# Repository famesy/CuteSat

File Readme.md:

# CubeSat PCB Design for Reliable Space Missions

CubeSat is an affordable and popular educational platform for deploying payloads into orbit. However, many university-level missions fail at a rate of around 50%. The primary reason for this is the difficulty of adapting an existing design, which results in poorly designed hardware for the harsh environment of space and a lack of failure handling software.

To address this problem, we have developed an expandable, low-cost printed circuit board (PCB) that can be stacked and includes the following components:

- Power supply unit
- Microcontroller
- Several sensors
- Watchdog
- Communication bus isolation
- External memory

We have used a component selection methodology that is based on existing research and adapted it to our design. We have also implemented a software Hamming error-correction code to protect the data.

Since our PCBs are modular, readers can design their own system using our design as a starting point. We offer failure handler software and hardware that can be easily integrated into their design. Our ultimate goal is to make space studies more accessible to everyone, increase the success rate, and allow people to focus on their missions rather than the hectic development.

Lastly, we intend to make our project open source so that it can continue to grow and improve over time. We hope that this project will develop into a community where people can discuss their designs and share their changes and knowledge for various missions.

Thank you for considering our CubeSat PCB design for your space mission needs.

## Project Components
This project includes two distinct folders: hardware and software.

### Hardware
The hardware folder contains four PCB designs that were used in our mission:

#### MCU (base PCB)

#### Motor driver (payload PCB)

#### Encoder (payload PCB)

#### ST-Link adapter

### Software
The software folder contains STM32 projects that include libraries for interfacing with the sensors and implementing error detection and correction algorithms.

### How its look when assemble

####Thank you for your interest in our project!

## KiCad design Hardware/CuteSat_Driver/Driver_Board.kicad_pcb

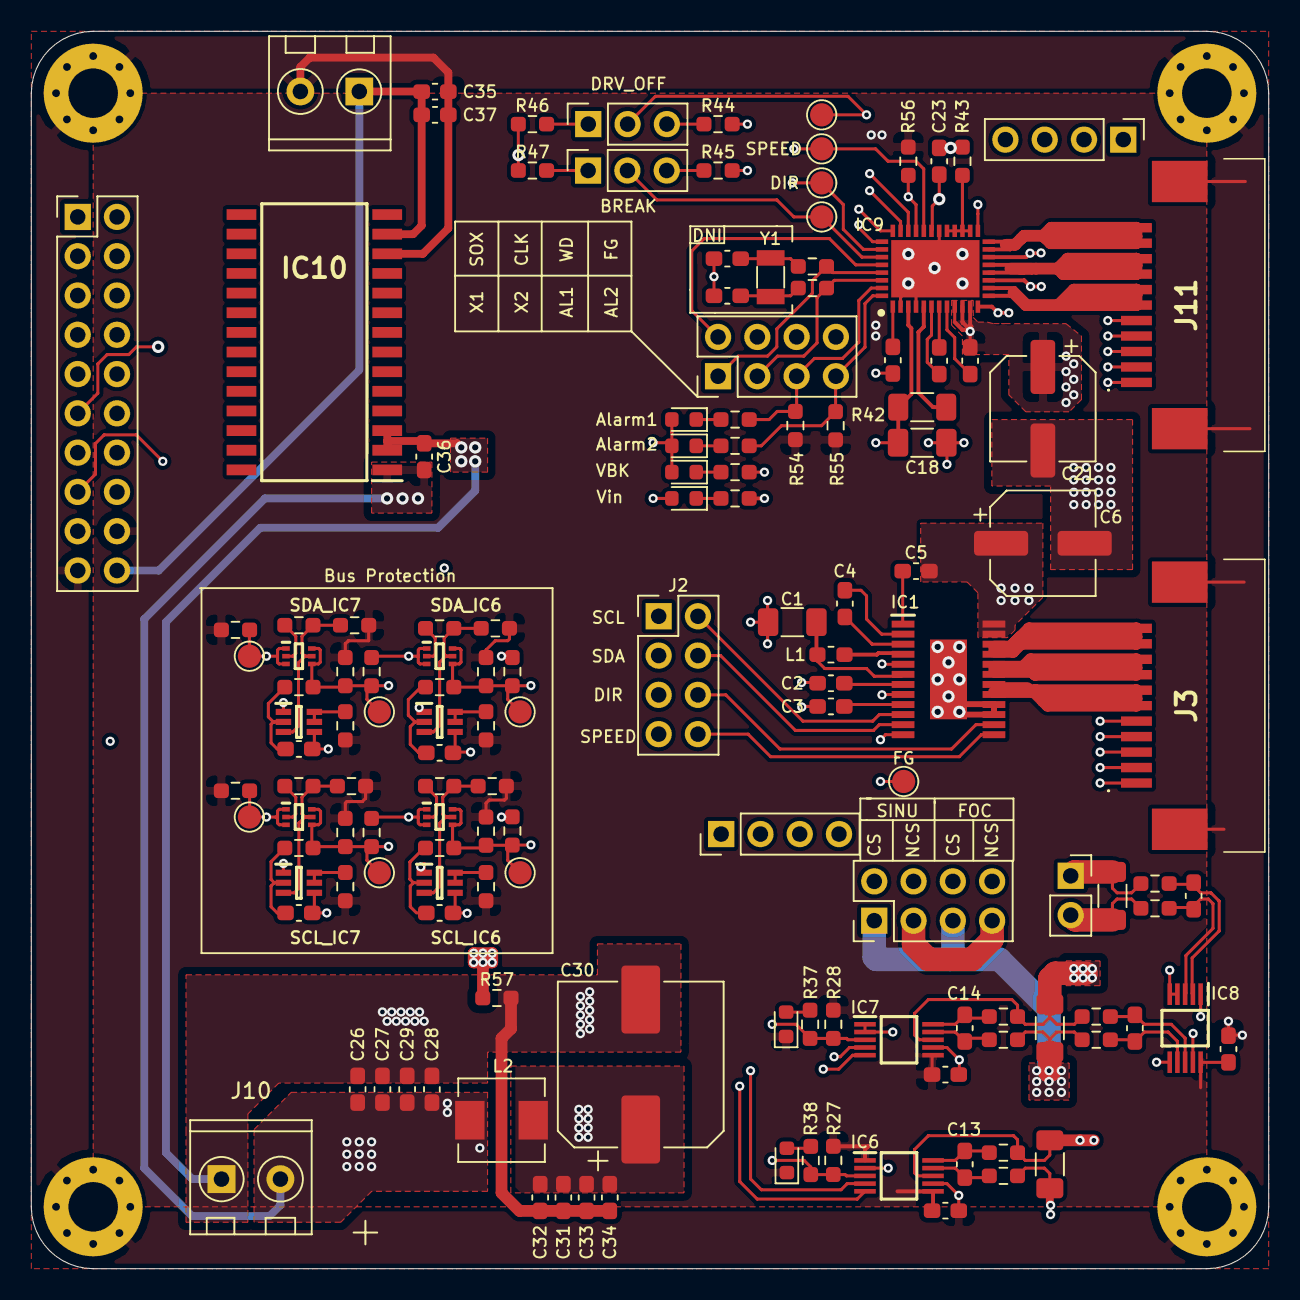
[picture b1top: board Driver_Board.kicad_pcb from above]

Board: 4 copper layers, 80.0 x 80.0 mm, 145 parts (0 on the bottom side), 109 nets.

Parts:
C1, C18: 22uF; C_1206_3216Metric_Pad1.33x1.80mm_HandSolder
C2, C3, C4, C5, C11, C12, C17, C27, C32, C35: 0.1uF; C_0603_1608Metric_Pad1.08x0.95mm_HandSolder
C6, C21: 100uF; CP_Elec_6.3x5.4_Nichicon
C7, C8, C9, C10: 10nF; C_0603_1608Metric_Pad1.08x0.95mm_HandSolder
C13, C14, C15, C16, C19, C20, C23, C26, C31, C37: 1uF; C_0603_1608Metric_Pad1.08x0.95mm_HandSolder
C22: 47nF; C_0603_1608Metric_Pad1.08x0.95mm_HandSolder
C24, C25: ??nF; C_0603_1608Metric_Pad1.08x0.95mm_HandSolder
C28, C33: 0.01uF; C_0603_1608Metric_Pad1.08x0.95mm_HandSolder
C29, C34: 1nF; C_0603_1608Metric_Pad1.08x0.95mm_HandSolder
C30: 330uF; CP_Elec_10x10.5
C36: 2.2uF; C_0603_1608Metric_Pad1.08x0.95mm_HandSolder
D1, D2, D3, D4, D5, D6: LED; LED_0603_1608Metric
H1, H2, H3, H4: MountingHole_Pad; MountingHole_3.2mm_M3_Pad_Via
IC1: DRV10975ZPWPR; SOP65P640X120-25N
IC2, IC3, IC4, IC5: MMDT2222V-7; SOTFL50P162X60-6N
IC6, IC7: INA238AIDGST; SOP50P490X110-10N
IC8: INA2181A2QDGSRQ1; SOP50P490X110-10N
IC9: MCF8316A; QFN50P500X700X100-41N-D
IC10: DCP021205U; SOIC127P1033X265-28N
J1: Pin header 2*10p; PinHeader_2x10_P2.54mm_Vertical
J2, J4, J9: Pin Header 2*4; PinHeader_2x04_P2.54mm_Vertical
J3, J11: 1-84953-1; 1849531
J5: Pin header 2p; PinSocket_1x02_P2.54mm_Vertical
J6, J7: Pin Header 3p; PinSocket_1x03_P2.54mm_Vertical
J8, J12: Pin Header 4p; PinHeader_1x04_P2.54mm_Vertical
J10: Screw Terminal 2p; terminal_2p_3.81
J13: Screw_Terminal_2p; terminal_2p_3.81
L1: 47uF; L_0603_1608Metric_Pad1.05x0.95mm_HandSolder
L2: 1nH; L_Sunlord_MWSA0518_5.4x5.2mm
Q1, Q2, Q3, Q4: BSS138DWQ-7; SOT65P210X110-6N
R1, R2, R7, R8, R9, R11, R13, R14, R19, R20, R21, R23, R25, R26, R27, R28, R44, R45, R46, R47, R54, R55, R56: 10k; R_0603_1608Metric_Pad0.98x0.95mm_HandSolder
R3, R4, R15, R16: 680; R_0603_1608Metric_Pad0.98x0.95mm_HandSolder
R5, R6, R17, R18: 0r; R_0603_1608Metric_Pad0.98x0.95mm_HandSolder
R10, R12, R22, R24: 200k; R_0603_1608Metric_Pad0.98x0.95mm_HandSolder
R29, R30, R32, R33, R35, R36, R39, R40: 10r; R_0603_1608Metric_Pad0.98x0.95mm_HandSolder
R31, R34, R41: 0.1r; R_1206_3216Metric_Pad1.30x1.75mm_HandSolder
R37, R38: 4,7k; R_0603_1608Metric_Pad0.98x0.95mm_HandSolder
R42: 22r; R_1206_3216Metric_Pad1.30x1.75mm_HandSolder
R43, R48, R49, R57: 0R; R_0603_1608Metric_Pad0.98x0.95mm_HandSolder
R50, R51, R52, R53: 1k; R_0603_1608Metric_Pad0.98x0.95mm_HandSolder
TP1, TP2, TP3, TP4, TP5, TP6, TP7, TP8, TP9, TP10, TP11: TestPoint; TestPoint_Pad_D1.5mm
Y1: Crystal; Crystal_SMD_3215-2Pin_3.2x1.5mm

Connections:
+3V3: C11.1, C12.1, C17.1, D1.1, D2.1, IC6.1, IC6.6, IC7.6, IC8.10, J1.18, R1.1, R2.1, R7.1, R8.1, R9.1, R11.1, R13.1, R14.1, R19.1, R20.1, R21.1, R23.1, R25.1, R26.1, R27.2, R28.2, R54.1, R55.1, R56.1
+5VA: C35.2, C37.2, IC10.13, J1.20, J13.1
+12P: C30.1, C31.1, C32.1, C33.1, C34.1, IC6.8, IC7.8, J4.3, J4.7, J5.2, L2.2, R29.1, R31.1, R32.1, R34.1, R35.2, R39.1, R41.1
/12V: J1.17, R30.1, R31.2
/12V_D1: C20.2, C21.1, D6.2, IC9.9, IC9.10, IC9.11, J4.6, J4.8
/12V_D2: C5.1, C6.1, IC1.23, IC1.24, J4.2, J4.4
/AL_INA238_1: IC7.3, J1.13, R28.1, R37.1
/AL_INA238_2: IC6.3, J1.15, R27.1, R38.1
/D1_BREAK: IC9.35, J1.5, J7.2, TP10.1
/D1_DIR: IC9.34, J1.3, TP9.1
/D1_DRVOFF: IC9.21, J1.7, J6.2, TP11.1
/D1_SPEED: IC9.28, J1.1, TP8.1
/D2_DIR: J1.11, J2.5
/D2_SPEED: J1.9, J2.7
/Driver_DRV10975/D2_DIR_I: IC1.14, J2.6
/Driver_DRV10975/D2_FG: IC1.12, TP1.1
/Driver_DRV10975/D2_SCL_I: IC1.10, J2.2
/Driver_DRV10975/D2_SDA_I: IC1.11, J2.4
/Driver_DRV10975/D2_SPEED_I: IC1.13, J2.8
/Driver_DRV10975/U: IC1.17, IC1.18, J3.6, J3.7
/Driver_DRV10975/V: IC1.19, IC1.20, J3.8, J3.9
/Driver_DRV10975/W: IC1.21, IC1.22, J3.10, J3.11
/Driver_MCF8316A/AVDD: C23.1, IC9.27, R46.1, R47.1
/Driver_MCF8316A/D1_A: IC9.13, IC9.14, J11.6, J11.7
/Driver_MCF8316A/D1_B: IC9.16, IC9.17, J11.8, J11.9
/Driver_MCF8316A/D1_C: IC9.19, IC9.20, J11.10, J11.11
/Driver_MCF8316A/VBK: C18.1, D3.2, D4.2, D5.2, IC9.3, R42.2
/Power Input & Filter/+12V_in: C26.1, C27.1, C28.1, C29.1, C36.1, IC10.1, J10.2, L2.1
/Power_Monitoring/12v_Power: J4.1, J4.5, R33.1, R34.2, R36.2
/SCL_Buspro: IC3.1, IC3.3, IC5.1, IC5.3, J1.12, R6.2, R18.2, R26.2, TP3.1
/SCL_D1: IC9.31, J1.4
/SCL_D2: J1.8, J2.1
/SDA_Buspro: IC2.1, IC2.3, IC4.1, IC4.3, J1.10, R5.2, R17.2, R25.2, TP2.1
/SDA_D1: IC9.30, J1.2
/SDA_D2: J1.6, J2.3
/ToADC_Sense1: IC8.1, J1.14
/ToADC_Sense2: IC8.9, J1.16
/scl_power1: IC3.4, IC3.6, IC7.5, R6.1, R11.2, R12.1, TP5.1
/scl_power2: IC5.4, IC5.6, IC6.5, R18.1, R23.2, R24.1, TP7.1
/sda_power1: IC2.4, IC2.6, IC7.4, R5.1, R9.2, R10.1, TP4.1
/sda_power2: IC4.4, IC4.6, IC6.4, R17.1, R21.2, R22.1, TP6.1
D1_Alarm1: IC9.39, J9.5, R51.2, R54.2
D1_Alarm2: IC9.40, J9.7, R52.2, R55.2
D1_EXT_CLK: IC9.33, J9.4
D1_EXT_WD: IC9.32, J9.6
D1_FG: IC9.29, J9.8, R56.2
D1_SOX: IC9.36, J9.2
D1_X1: IC9.37, J9.1, R48.2
D1_X2: IC9.38, J9.3, R49.1
GND: C1.1, C2.2, C3.1, C7.2, C8.2, C9.2, C10.2, C11.2, C12.2, C17.2, C18.2, C19.2, C23.2, C24.2, C25.2, C35.1, C37.1, H1.1, H2.1, H3.1, H4.1, IC1.5, IC1.8, IC6.2, IC6.7, IC7.1, IC7.2, IC7.7, IC8.4, IC8.5, IC8.6, IC9.2, IC9.4, IC9.26, IC9.41, IC10.12, J1.19, J3.5, J3.MP1, J3.MP2, J11.5, J11.MP1, J11.MP2, J13.2, Q1.1, Q1.4, Q2.1, Q2.4, Q3.1, Q3.4, Q4.1, Q4.4, R43.1, R44.2, R45.2, R50.2, R57.2
GNDPWR: C6.2, C21.2, C26.2, C27.2, C28.2, C29.2, C30.2, C31.2, C32.2, C33.2, C34.2, C36.2, IC1.15, IC1.16, IC1.25, IC9.12, IC9.15, IC9.18, IC10.2, IC10.3, J10.1, R53.2, R57.1
unnamed: C1.2, IC1.6, L1.1
unnamed: C2.1, IC1.7
unnamed: C3.2, IC1.9
unnamed: C4.1, IC1.2
unnamed: C4.2, IC1.3
unnamed: C5.2, IC1.1
unnamed: C7.1, Q1.2, R10.2
unnamed: C8.1, Q2.2, R12.2
unnamed: C9.1, Q3.2, R22.2
unnamed: C10.1, Q4.2, R24.2
unnamed: C13.1, IC6.10, R29.2
unnamed: C13.2, IC6.9, R30.2
unnamed: C19.1, IC9.1
unnamed: C20.1, IC9.8
unnamed: C22.1, IC9.6
unnamed: C22.2, IC9.7
unnamed: C24.1, R48.1, Y1.1
unnamed: C25.1, R49.2, Y1.2
unnamed: D1.2, R37.2
unnamed: D2.2, R38.2
unnamed: D3.1, R50.1
unnamed: D4.1, R51.1
unnamed: D5.1, R52.1
unnamed: D6.1, R53.1
unnamed: IC1.4, L1.2
unnamed: IC2.2, R3.1
unnamed: IC2.5, Q1.3, R1.2, R3.2
unnamed: IC3.2, R4.1
unnamed: IC3.5, Q2.3, R2.2, R4.2
unnamed: IC4.2, R15.1
unnamed: IC4.5, Q3.3, R13.2, R15.2
unnamed: IC5.2, R16.1
unnamed: IC5.5, Q4.3, R14.2, R16.2
unnamed: IC9.5, R42.1
unnamed: IC9.22, IC9.23, IC9.24, IC9.25, R43.2
unnamed: J3.1, J8.4
unnamed: J3.2, J8.3
unnamed: J3.3, J8.2
unnamed: J3.4, J8.1
unnamed: J5.1, R40.1, R41.2
unnamed: J6.1, R46.2
unnamed: J6.3, R44.1
unnamed: J7.1, R47.2
unnamed: J7.3, R45.1
unnamed: J11.1, J12.4
unnamed: J11.2, J12.3
unnamed: J11.3, J12.2
unnamed: J11.4, J12.1
unnamed: Q1.5, Q1.6, R7.2
unnamed: Q2.5, Q2.6, R8.2
unnamed: Q3.5, Q3.6, R19.2
unnamed: Q4.5, Q4.6, R20.2
Rsense+: C16.1, IC8.3, R39.2
Rsense-: C16.2, IC8.2, R40.2
RsenseA_IN+: C14.1, IC7.10, R32.2
RsenseA_IN-: C14.2, IC7.9, R33.2
RsenseB_IN+: C15.1, IC8.8, R35.1
RsenseB_IN-: C15.2, IC8.7, R36.1

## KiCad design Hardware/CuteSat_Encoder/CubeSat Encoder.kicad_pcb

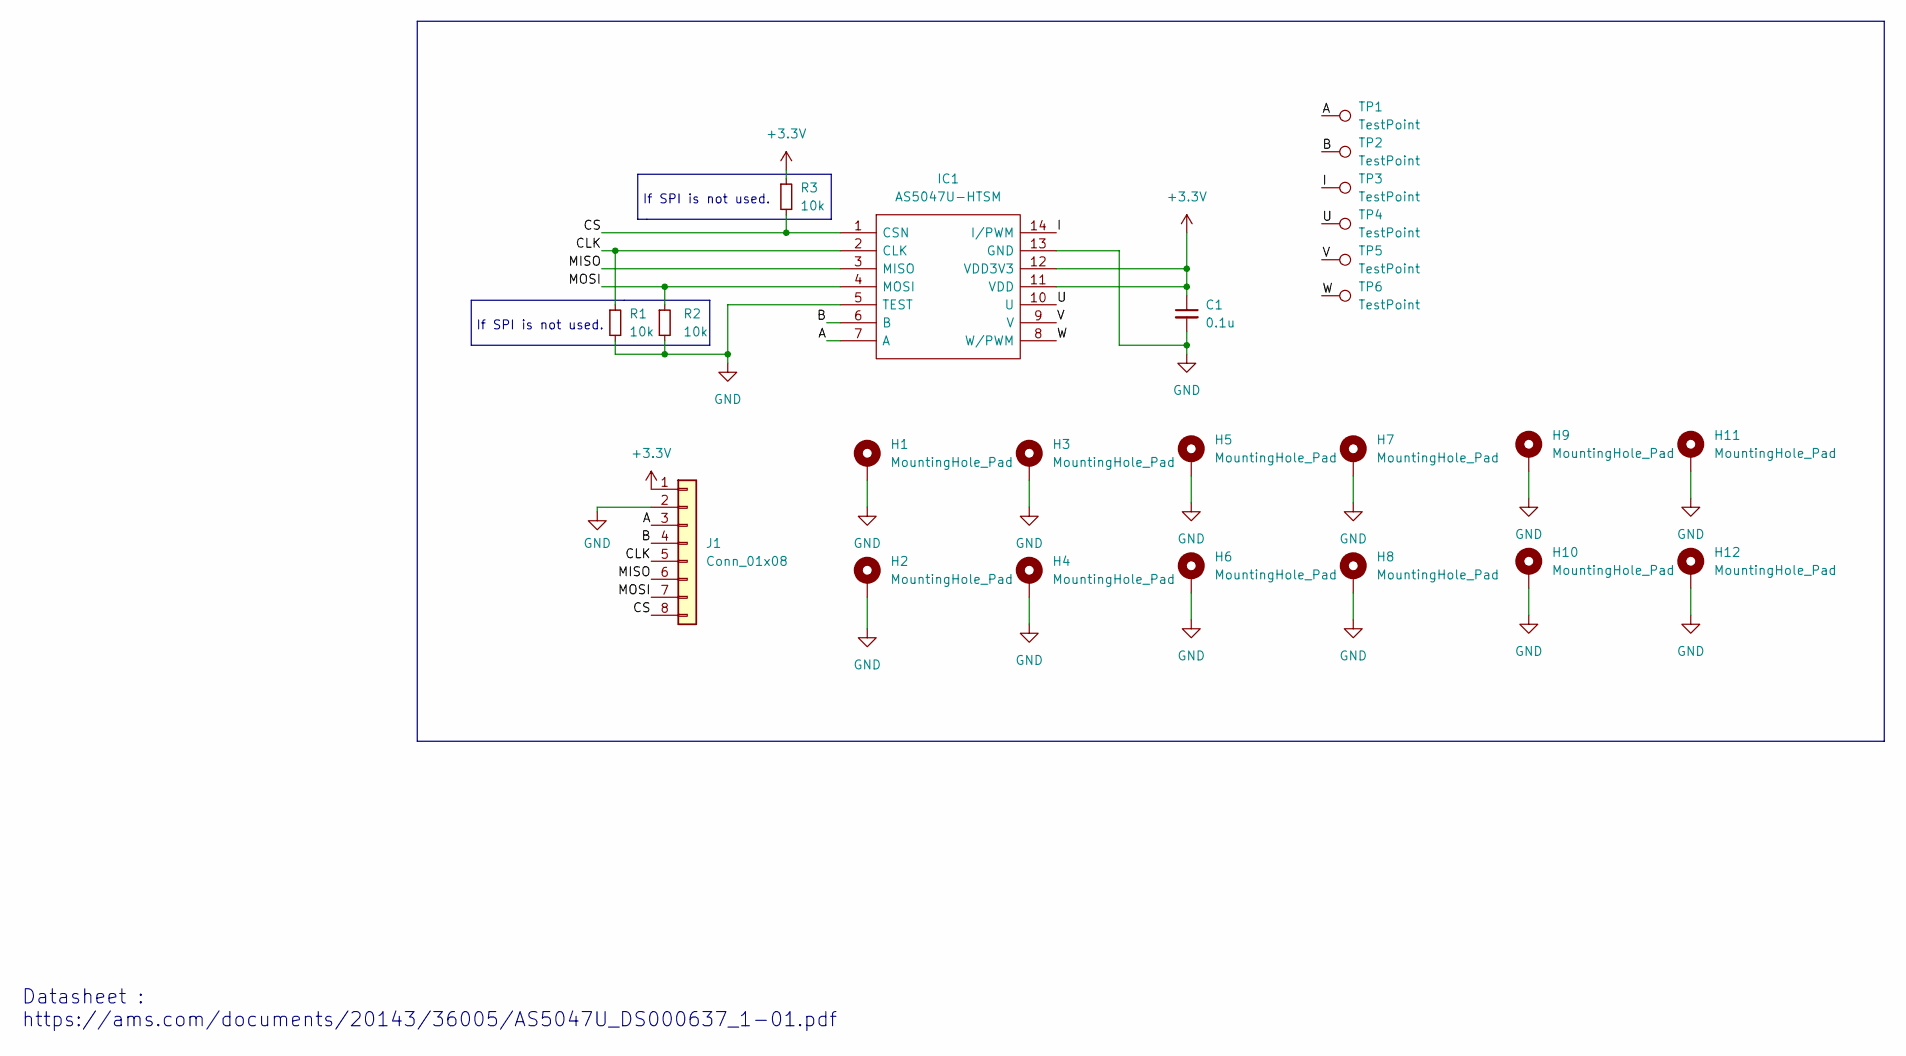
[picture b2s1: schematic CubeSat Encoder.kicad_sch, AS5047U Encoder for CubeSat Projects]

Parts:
C1: 0.1u; C_0603_1608Metric_Pad1.08x0.95mm_HandSolder
H1, H2, H3, H4, H5, H6, H7, H8, H9, H10, H11, H12: MountingHole_Pad; MountingHole_2.2mm_M2_Pad_Via
IC1: AS5047U-HTSM; SOP65P640X120-14N; Manufacturer_Part_Number AS5047U-HTSM; Mouser Part Number 985-AS5047U-HTSM
J1: Conn_01x08; JST_XH_S8B-XH-A-1_1x08_P2.50mm_Horizontal
R1, R2, R3: 10k; R_0603_1608Metric_Pad0.98x0.95mm_HandSolder
TP1, TP2, TP3, TP4, TP5, TP6: TestPoint; TestPoint_Pad_1.0x1.0mm

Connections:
+3V3: C1.1, IC1.11 (VDD), IC1.12 (VDD3V3), J1.1, R3.1
/A: IC1.7 (A), J1.3, TP1.1
/B: IC1.6 (B), J1.4, TP2.1
/CLK: IC1.2 (CLK), J1.5, R1.1
/CS: IC1.1 (CSN), J1.8, R3.2
/I: IC1.14 (I/PWM), TP3.1
/MISO: IC1.3 (MISO), J1.6
/MOSI: IC1.4 (MOSI), J1.7, R2.1
/U: IC1.10 (U), TP4.1
/V: IC1.9 (V), TP5.1
/W: IC1.8 (W/PWM), TP6.1
GND: C1.2, H1.1, H2.1, H3.1, H4.1, H5.1, H6.1, H7.1, H8.1, H9.1, H10.1, H11.1, H12.1, IC1.5 (TEST), IC1.13 (GND), J1.2, R1.2, R2.2

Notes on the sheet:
If SPI is not used.
Datasheet : https://ams.com/documents/20143/36005/AS5047U_DS000637_1-01.pdf

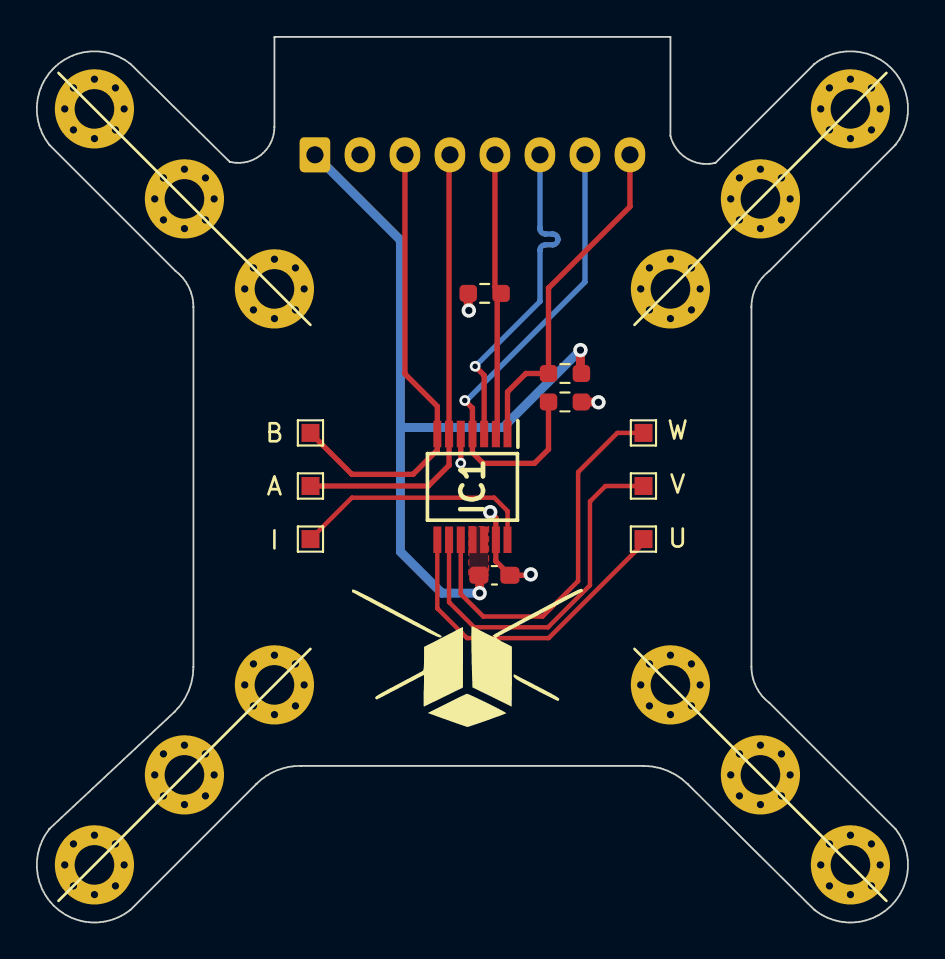
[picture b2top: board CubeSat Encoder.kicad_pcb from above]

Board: 4 copper layers, 48.4 x 49.2 mm, 24 parts (1 on the bottom side), 12 nets.

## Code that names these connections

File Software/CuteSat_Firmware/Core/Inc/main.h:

/* USER CODE BEGIN Header */
/**
  ******************************************************************************
  * @file           : main.h
  * @brief          : Header for main.c file.
  *                   This file contains the common defines of the application.
  ******************************************************************************
  * @attention
  *
  * Copyright (c) 2022 STMicroelectronics.
  * All rights reserved.
  *
  * This software is licensed under terms that can be found in the LICENSE file
  * in the root directory of this software component.
  * If no LICENSE file comes with this software, it is provided AS-IS.
  *
  ******************************************************************************
  */
/* USER CODE END Header */

/* Define to prevent recursive inclusion -------------------------------------*/
#ifndef __MAIN_H
#define __MAIN_H

#ifdef __cplusplus
extern "C" {
#endif

/* Includes ------------------------------------------------------------------*/
#include "stm32h7xx_hal.h"

/* Private includes ----------------------------------------------------------*/
/* USER CODE BEGIN Includes */

/* USER CODE END Includes */

/* Exported types ------------------------------------------------------------*/
/* USER CODE BEGIN ET */

/* USER CODE END ET */

/* Exported constants --------------------------------------------------------*/
/* USER CODE BEGIN EC */

/* USER CODE END EC */

/* Exported macro ------------------------------------------------------------*/
/* USER CODE BEGIN EM */

/* USER CODE END EM */

/* Exported functions prototypes ---------------------------------------------*/
void Error_Handler(void);

/* USER CODE BEGIN EFP */

/* USER CODE END EFP */

/* Private defines -----------------------------------------------------------*/
#define D1_DIR_Pin GPIO_PIN_4
#define D1_DIR_GPIO_Port GPIOE
#define D1_SPEED_Pin GPIO_PIN_5
#define D1_SPEED_GPIO_Port GPIOE
#define TEMP_ALERT_Pin GPIO_PIN_2
#define TEMP_ALERT_GPIO_Port GPIOF
#define D2_SPEED_Pin GPIO_PIN_7
#define D2_SPEED_GPIO_Port GPIOF
#define D2_DIR_Pin GPIO_PIN_8
#define D2_DIR_GPIO_Port GPIOF
#define ALERT_INA238_1_Pin GPIO_PIN_2
#define ALERT_INA238_1_GPIO_Port GPIOC
#define ALERT_INA238_2_Pin GPIO_PIN_3
#define ALERT_INA238_2_GPIO_Port GPIOC
#define SPI1_CS_Pin GPIO_PIN_4
#define SPI1_CS_GPIO_Port GPIOA
#define LED4_Pin GPIO_PIN_14
#define LED4_GPIO_Port GPIOF
#define LED3_Pin GPIO_PIN_15
#define LED3_GPIO_Port GPIOF
#define LED2_Pin GPIO_PIN_0
#define LED2_GPIO_Port GPIOG
#define LED1_Pin GPIO_PIN_1
#define LED1_GPIO_Port GPIOG
#define FRAM_CS_Pin GPIO_PIN_12
#define FRAM_CS_GPIO_Port GPIOB
#define FRAM_HOLD_Pin GPIO_PIN_8
#define FRAM_HOLD_GPIO_Port GPIOD
#define FRAM_WP_Pin GPIO_PIN_9
#define FRAM_WP_GPIO_Port GPIOD
#define SDMMC_DETECT_Pin GPIO_PIN_0
#define SDMMC_DETECT_GPIO_Port GPIOD
#define SPI6_CS_Pin GPIO_PIN_11
#define SPI6_CS_GPIO_Port GPIOG
#define WDI2_Pin GPIO_PIN_0
#define WDI2_GPIO_Port GPIOE
#define WDI1_Pin GPIO_PIN_1
#define WDI1_GPIO_Port GPIOE
/* USER CODE BEGIN Private defines */

/* USER CODE END Private defines */

#ifdef __cplusplus
}
#endif

#endif /* __MAIN_H */

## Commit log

2023-04-01 Add All files
